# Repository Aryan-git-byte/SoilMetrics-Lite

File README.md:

# What is SoilMetric-Lite??
it is a compact soil health monitoring system based on a MAX485 and Atmega328P. its job is to interface the ZTS-3002-TR-ECTHNPKPH-N01 RS485 to a device such as PC, Laptop or phone.
You can even use this board to operate other RS485 based devices.
With the help of this sensor: [ZTS-3002-TR-ECTHNPKPH-N01 RS485](https://robu-prod-media.s3.ap-south-1.amazonaws.com/uploads/2025/04/R224073R224074-ZTS-3002-TR-N01.pdf) it can measure NPK, EC, pH, Temperature and Moisture of the soil.

# Schematic Overview:

Over here, you can see the schematic of the project. The schematic mainly consists of a USB port, a CH340C, a ATMEGA328P and MAX485.
# PCB Overview:
For this project, I used a double layer PCB with a compact layout, which u can see here:

Also heres a cool render of the pcb:

# Case Overview:

The enclosure of this project is designed in fusion 360, the source file of which i have provided in `cad/fusion/` 
The enclosure have 2 parts:
- top body
- bottom body
both of which snaps together easily with pcb in middle.
# Firmware:
It is a simple firmware written in `.ino` which u can upload to the board using ICSP header, but fist you'll have to burn it.

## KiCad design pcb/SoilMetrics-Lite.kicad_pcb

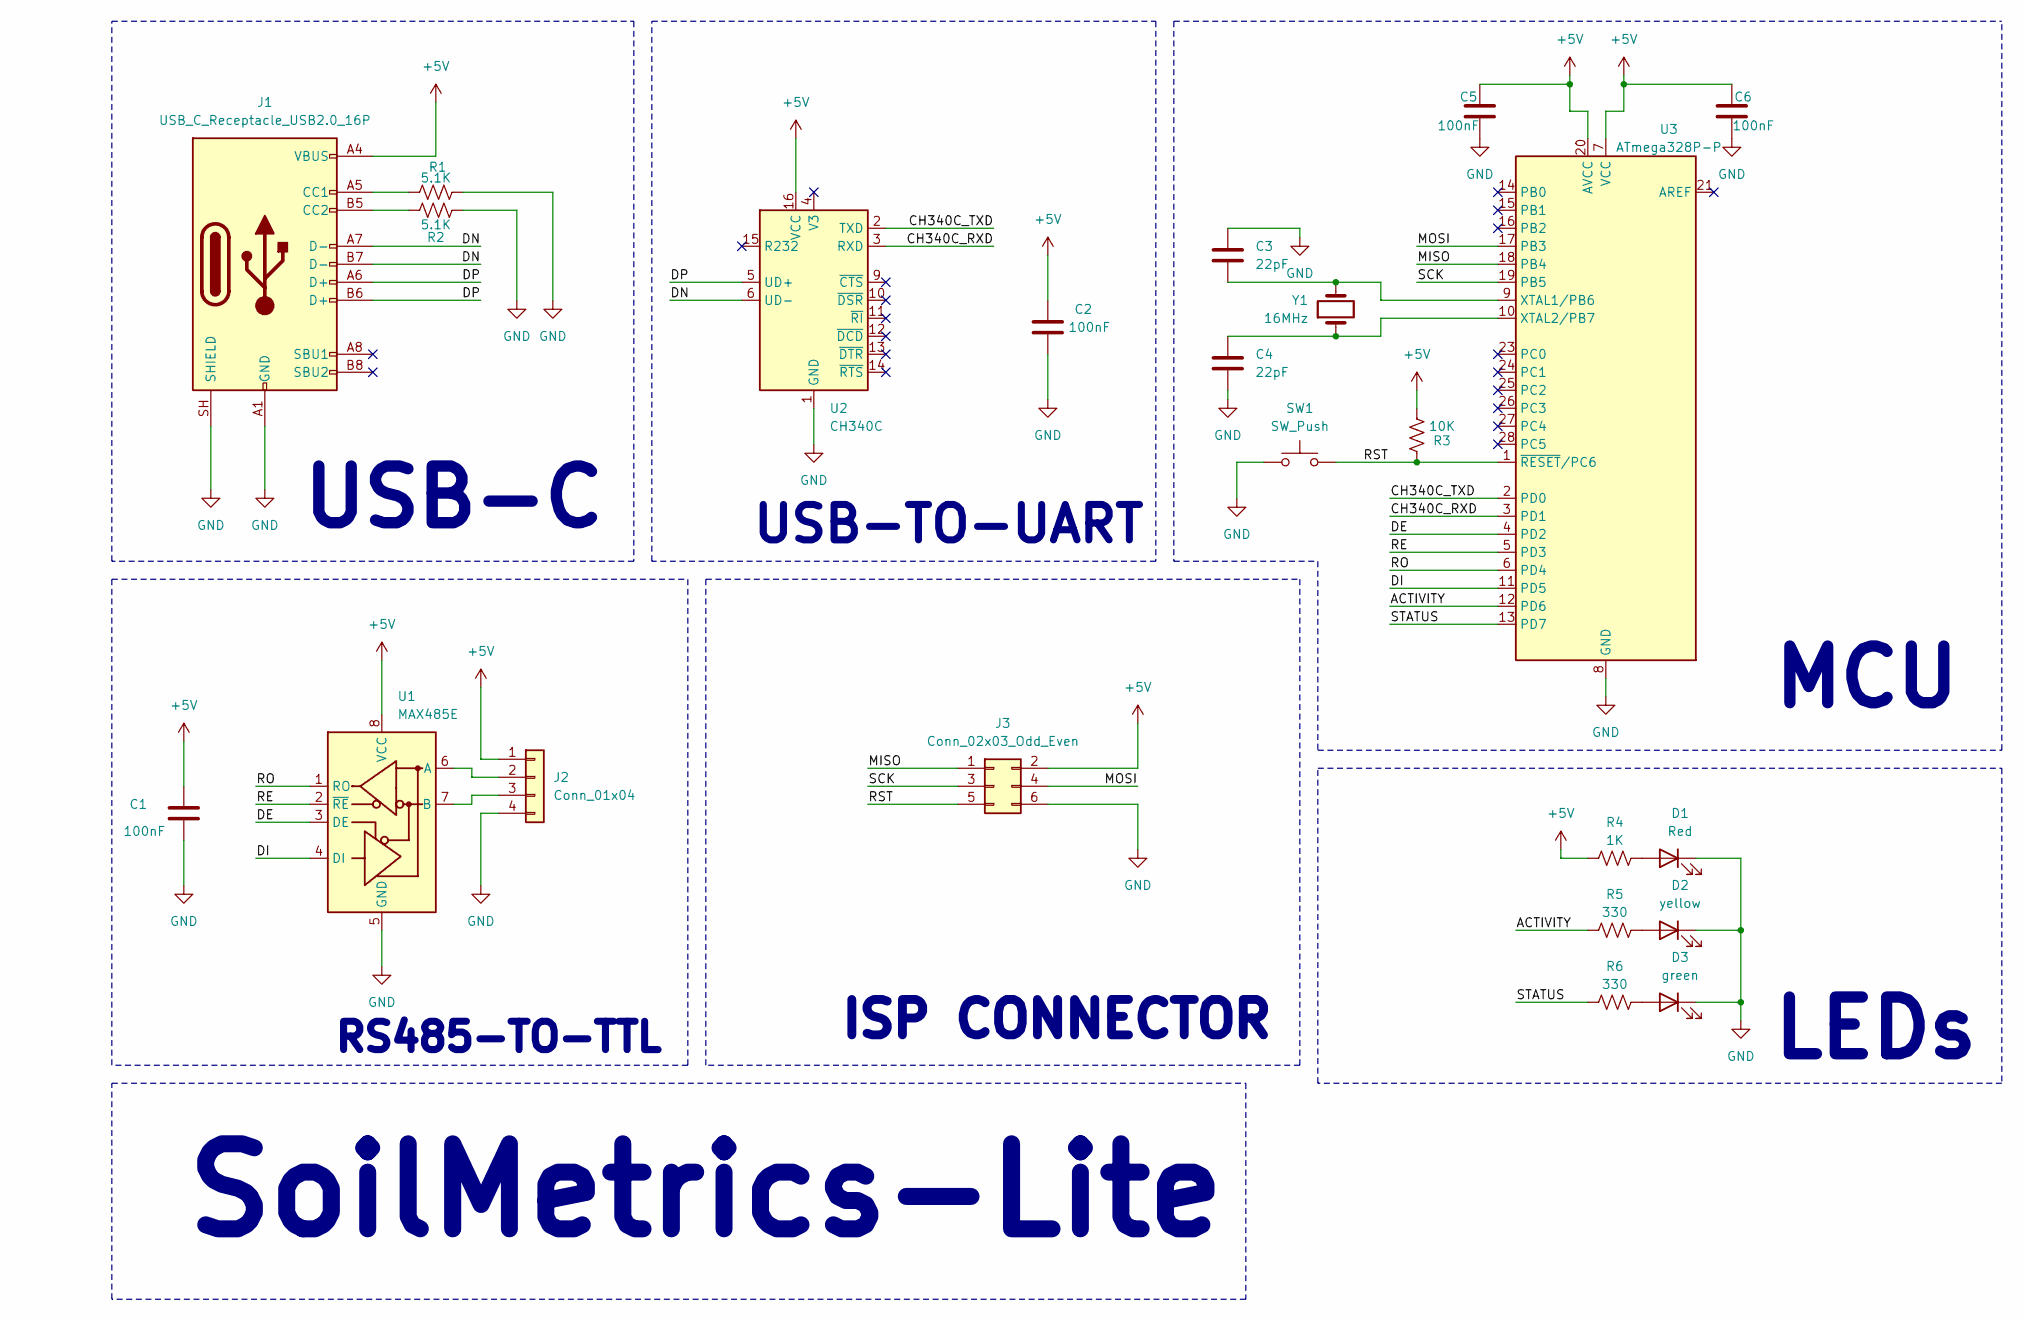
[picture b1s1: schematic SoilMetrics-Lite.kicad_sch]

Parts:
C1, C2, C5, C6: 100nF; C_0805_2012Metric_Pad1.18x1.45mm_HandSolder
C3, C4: 22pF; C_0805_2012Metric_Pad1.18x1.45mm_HandSolder
D1: Red; LED_D3.0mm
D2: yellow; LED_D3.0mm
D3: green; LED_D3.0mm
J1: USB_C_Receptacle_USB2.0_16P; USB_C_Receptacle_GCT_USB4105-xx-A_16P_TopMnt_Horizontal
J2: Conn_01x04; PinHeader_1x04_P2.54mm_Vertical
J3: Conn_02x03_Odd_Even; PinHeader_2x03_P2.54mm_Vertical
R1, R2: 5.1K; R_0805_2012Metric_Pad1.20x1.40mm_HandSolder
R3: 10K; R_0805_2012Metric_Pad1.20x1.40mm_HandSolder
R4: 1K; R_0805_2012Metric_Pad1.20x1.40mm_HandSolder
R5, R6: 330; R_0805_2012Metric_Pad1.20x1.40mm_HandSolder
SW1: SW_Push; SW_TH_Tactile_Omron_B3F-107x
U1: MAX485E; SOIC-8_3.9x4.9mm_P1.27mm
U2: CH340C; SOIC-16_3.9x9.9mm_P1.27mm
U3: ATmega328P-P; DIP-28_W7.62mm
Y1: 16MHz; Crystal_HC49-4H_Vertical

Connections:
+5V: C1.1, C2.1, C5.1, C6.1, J1.A4 (VBUS), J1.A9 (VBUS), J1.B4 (VBUS), J1.B9 (VBUS), J2.1, J3.2, R3.1, R4.1, U1.8 (VCC), U2.16 (VCC), U3.7 (VCC), U3.20 (AVCC)
/ACTIVITY: R5.1, U3.12 (PD6)
/CH340C_RXD: U2.3 (RXD), U3.3 (PD1)
/CH340C_TXD: U2.2 (TXD), U3.2 (PD0)
/DE: U1.3 (DE), U3.4 (PD2)
/DI: U1.4 (DI), U3.11 (PD5)
/DN: J1.A7 (D-), J1.B7 (D-), U2.6 (UD-)
/DP: J1.A6 (D+), J1.B6 (D+), U2.5 (UD+)
/MISO: J3.1, U3.18 (PB4)
/MOSI: J3.4, U3.17 (PB3)
/RE: U1.2 (~RE), U3.5 (PD3)
/RO: U1.1 (RO), U3.6 (PD4)
/RST: J3.5, R3.2, SW1.2, U3.1 (~RESET/PC6)
/SCK: J3.3, U3.19 (PB5)
/STATUS: R6.1, U3.13 (PD7)
GND: C1.2, C2.2, C3.1, C4.2, C5.2, C6.2, D1.1 (K), D2.1 (K), D3.1 (K), J1.A1 (GND), J1.A12 (GND), J1.B1 (GND), J1.B12 (GND), J1.SH (SHIELD), J2.4, J3.6, R1.2, R2.1, SW1.1, U1.5 (GND), U2.1 (GND), U3.8 (GND), U3.22 (GND)
unnamed: D1.2 (A), R4.2
unnamed: D2.2 (A), R5.2
unnamed: D3.2 (A), R6.2
unnamed: J1.A5 (CC1), R1.1
unnamed: J1.B5 (CC2), R2.2
unnamed: J2.2, U1.6 (A)
unnamed: J2.3, U1.7 (B)
unnamed: C3.2, U3.9 (XTAL1/PB6), Y1.2
unnamed: C4.1, U3.10 (XTAL2/PB7), Y1.1

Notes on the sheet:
SoilMetrics-Lite
USB-C
LEDs
ISP CONNECTOR
RS485-TO-TTL
MCU
USB-TO-UART

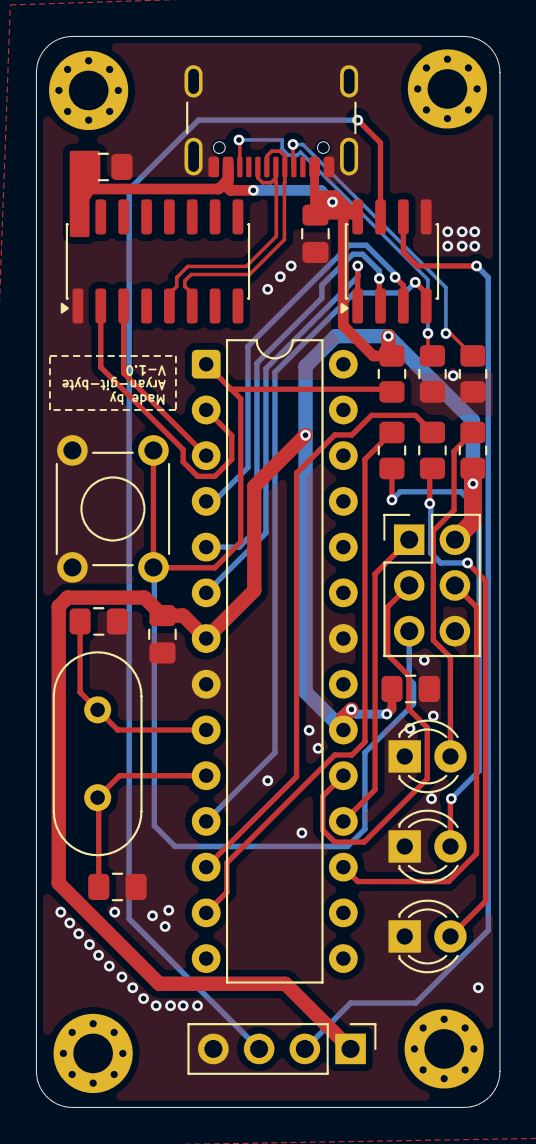
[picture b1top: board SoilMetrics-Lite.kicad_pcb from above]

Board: 2 copper layers, 25.8 x 59.5 mm, 23 parts (0 on the bottom side), 25 nets.
